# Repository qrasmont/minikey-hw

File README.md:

# Minikey

Mini is a macropad.

## Rev 0.1

### Rev 0.1 Issues

Only related to the BOM.
- Button were not assembled
- R2,R3 are 27K instead of 27 Ohm.

# Characteristics

- 2 rotatry encoders
- 16 keys (Cherry MX, hot swappable)
- USB-C
- RP2040 MCU

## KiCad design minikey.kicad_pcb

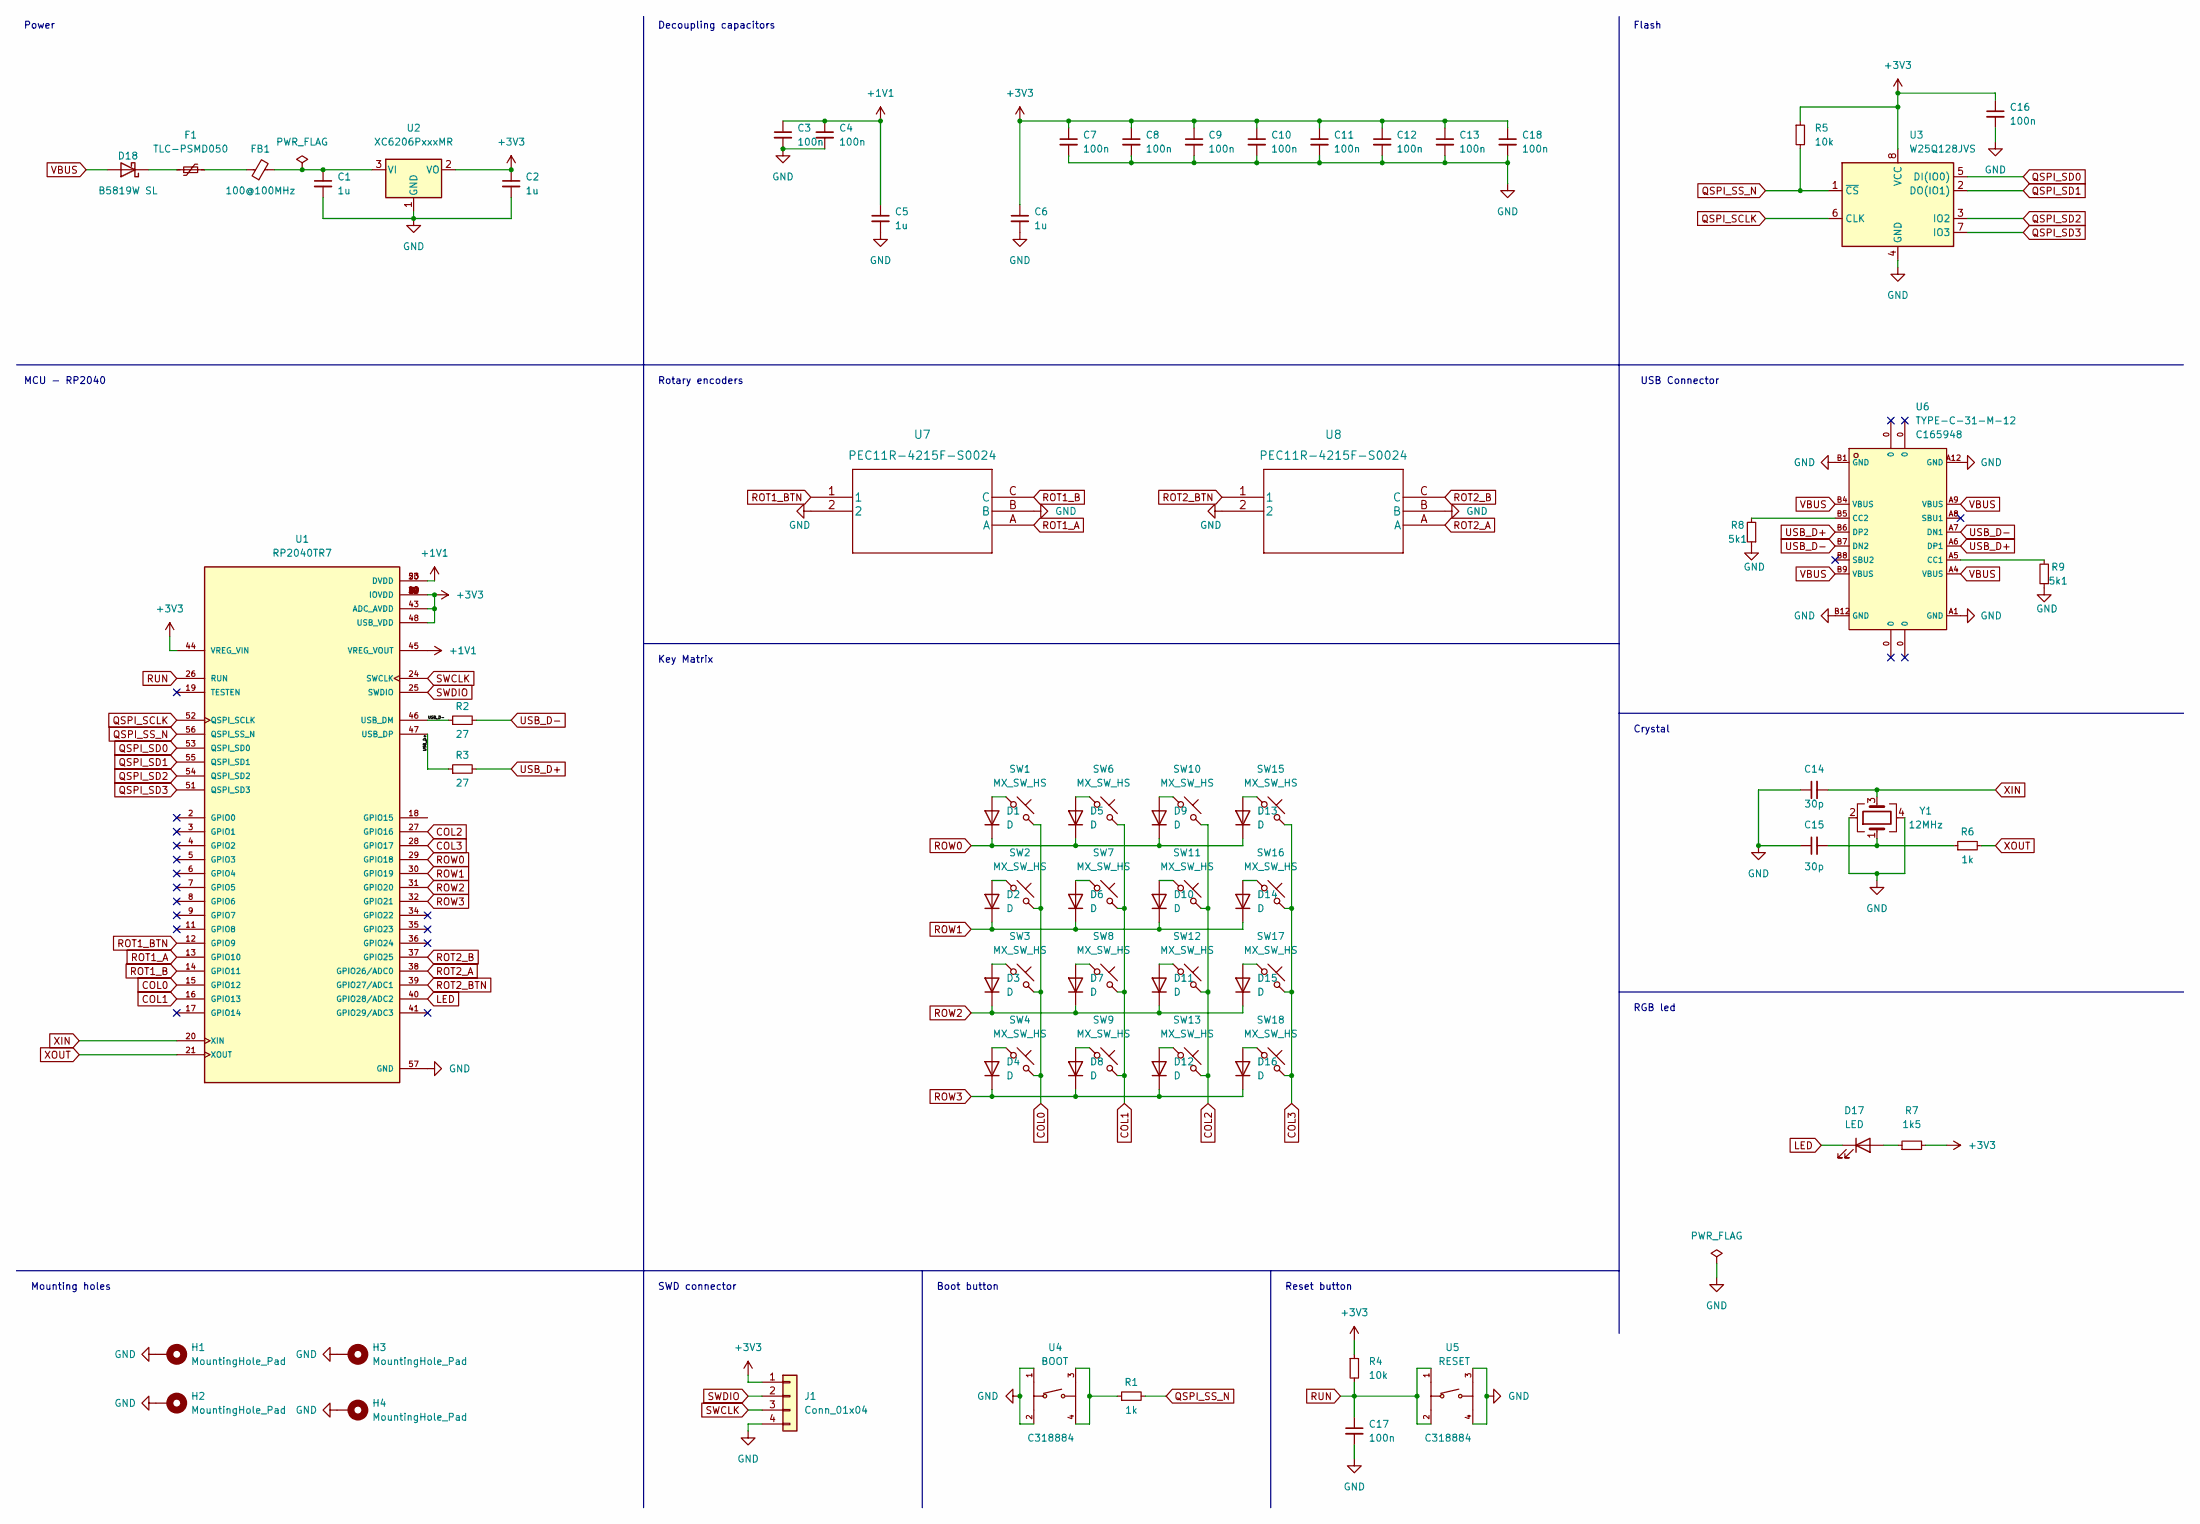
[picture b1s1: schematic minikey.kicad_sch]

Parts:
C1, C2, C5, C6: 1u; C_0402_1005Metric; LCSC Part # C52923
C3, C4, C7, C8, C9, C10, C11, C12, C13, C16, C17, C18: 100n; C_0402_1005Metric; LCSC Part # C307331
C14, C15: 30p; C_0402_1005Metric; LCSC Part # C1570
D1, D2, D3, D4, D5, D6, D7, D8, D9, D10, D11, D12, D13, D14, D15, D16: D; D_SOD-123; LCSC Part # C81598
D17: LED; LED_0805_2012Metric; LCSC Part # C2297
D18: B5819W SL; D_SOD-123; LCSC Part # C8598
F1: TLC-PSMD050; Fuse_0805_2012Metric; LCSC Part # C261942
FB1: 100@100MHz; L_0805_2012Metric; LCSC Part # C1015
H1, H2, H3, H4: MountingHole_Pad; MountingHole_2.2mm_M2_Pad_Via
J1: Conn_01x04; PinHeader_1x04_P2.54mm_Vertical
R1, R6: 1k; R_0402_1005Metric; LCSC Part # C11702
R2, R3: 27; R_0402_1005Metric; LCSC Part # C25190
R4, R5: 10k; R_0402_1005Metric; LCSC Part # C25744
R7: 1k5; R_0402_1005Metric; LCSC Part # C25867
R8, R9: 5k1; R_0402_1005Metric; LCSC Part # C25905
SW1, SW2, SW3, SW4, SW6, SW7, SW8, SW9, SW10, SW11, SW12, SW13, SW15, SW16, SW17, SW18: MX_SW_HS; SW_MX_HS_1u
U1: RP2040TR7; QFN40P700X700X90-57N; PARTREV 1.7.1; LCSC Part # C2040
U2: XC6206PxxxMR; SOT-23; LCSC Part # C5446
U3: W25Q128JVS; SOIC-8_5.23x5.23mm_P1.27mm; LCSC Part # C97521
U4: BOOT; tactile-switch; LCSC C318884
U5: RESET; tactile-switch; LCSC C318884
U6: TYPE-C-31-M-12; simple-usb-c; LCSC C165948
U7, U8: PEC11R-4215F-S0024
Y1: 12MHz; Crystal_SMD_3225-4Pin_3.2x2.5mm; LCSC Part # C9002

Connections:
+1V1: C3.1, C4.1, C5.1, U1.23 (DVDD), U1.45 (VREG_VOUT), U1.50 (DVDD)
+3V3: C2.1, C6.1, C7.1, C8.1, C9.1, C10.1, C11.1, C12.1, C13.1, C16.1, C18.1, J1.1, R4.1, R5.1, R7.2, U1.1 (IOVDD), U1.10 (IOVDD), U1.22 (IOVDD), U1.33 (IOVDD), U1.42 (IOVDD), U1.43 (ADC_AVDD), U1.44 (VREG_VIN), U1.48 (USB_VDD), U1.49 (IOVDD), U2.2 (VO), U3.8 (VCC)
COL0: SW1.2, SW2.2, SW3.2, SW4.2, U1.15 (GPIO12)
COL1: SW6.2, SW7.2, SW8.2, SW9.2, U1.16 (GPIO13)
COL2: SW10.2, SW11.2, SW12.2, SW13.2, U1.27 (GPIO16)
COL3: SW15.2, SW16.2, SW17.2, SW18.2, U1.28 (GPIO17)
GND: C1.2, C2.2, C3.2, C4.2, C5.2, C6.2, C7.2, C8.2, C9.2, C10.2, C11.2, C12.2, C13.2, C14.1, C15.1, C16.2, C17.2, C18.2, H1.1, H2.1, H3.1, H4.1, J1.4, R8.1, R9.1, U1.57 (GND), U2.1 (GND), U3.4 (GND), U4.1 (A), U4.2 (B), U5.3 (C), U5.4 (D), U6.A1 (GND), U6.A12 (GND), U6.B1 (GND), U6.B12 (GND), U7.2, U7.B, U8.2, U8.B, Y1.2, Y1.4
LED: D17.1 (K), U1.40 (GPIO28/ADC2)
unnamed: C1.1, FB1.2, U2.3 (VI)
unnamed: C15.2, R6.1, Y1.1
unnamed: D1.2 (A), SW1.1
unnamed: D2.2 (A), SW2.1
unnamed: D3.2 (A), SW3.1
unnamed: D4.2 (A), SW4.1
unnamed: D5.2 (A), SW6.1
unnamed: D6.2 (A), SW7.1
unnamed: D7.2 (A), SW8.1
unnamed: D8.2 (A), SW9.1
unnamed: D9.2 (A), SW10.1
unnamed: D10.2 (A), SW11.1
unnamed: D11.2 (A), SW12.1
unnamed: D12.2 (A), SW13.1
unnamed: D13.2 (A), SW15.1
unnamed: D14.2 (A), SW16.1
unnamed: D15.2 (A), SW17.1
unnamed: D16.2 (A), SW18.1
unnamed: D17.2 (A), R7.1
unnamed: D18.1 (K), F1.1
unnamed: F1.2, FB1.1
unnamed: R1.1, U4.3 (C), U4.4 (D)
unnamed: R8.2, U6.B5 (CC2)
unnamed: R9.2, U6.A5 (CC1)
QSPI_SCLK: U1.52 (QSPI_SCLK), U3.6 (CLK)
QSPI_SD0: U1.53 (QSPI_SD0), U3.5 (DI(IO0))
QSPI_SD1: U1.55 (QSPI_SD1), U3.2 (DO(IO1))
QSPI_SD2: U1.54 (QSPI_SD2), U3.3 (IO2)
QSPI_SD3: U1.51 (QSPI_SD3), U3.7 (IO3)
QSPI_SS_N: R1.2, R5.2, U1.56 (QSPI_SS_N), U3.1 (~CS)
ROT1_A: U1.13 (GPIO10), U7.A
ROT1_B: U1.14 (GPIO11), U7.C
ROT1_BTN: U1.12 (GPIO9), U7.1
ROT2_A: U1.38 (GPIO26/ADC0), U8.A
ROT2_B: U1.37 (GPIO25), U8.C
ROT2_BTN: U1.39 (GPIO27/ADC1), U8.1
ROW0: D1.1 (K), D5.1 (K), D9.1 (K), D13.1 (K), U1.29 (GPIO18)
ROW1: D2.1 (K), D6.1 (K), D10.1 (K), D14.1 (K), U1.30 (GPIO19)
ROW2: D3.1 (K), D7.1 (K), D11.1 (K), D15.1 (K), U1.31 (GPIO20)
ROW3: D4.1 (K), D8.1 (K), D12.1 (K), D16.1 (K), U1.32 (GPIO21)
RUN: C17.1, R4.2, U1.26 (RUN), U5.1 (A), U5.2 (B)
SWCLK: J1.3, U1.24 (SWCLK)
SWDIO: J1.2, U1.25 (SWDIO)
USB_D+: R3.1, R3.2, U1.47 (USB_DP), U6.A6 (DP1), U6.B6 (DP2)
USB_D-: R2.1, R2.2, U1.46 (USB_DM), U6.A7 (DN1), U6.B7 (DN2)
VBUS: D18.2 (A), U6.A4 (VBUS), U6.A9 (VBUS), U6.B4 (VBUS), U6.B9 (VBUS)
XIN: C14.2, U1.20 (XIN), Y1.3
XOUT: R6.2, U1.21 (XOUT)

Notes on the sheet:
Reset button
Mounting holes
Decoupling capacitors
Power
USB Connector
Rotary encoders
Flash
Crystal
SWD connector
RGB led
Key Matrix
MCU - RP2040
Boot button

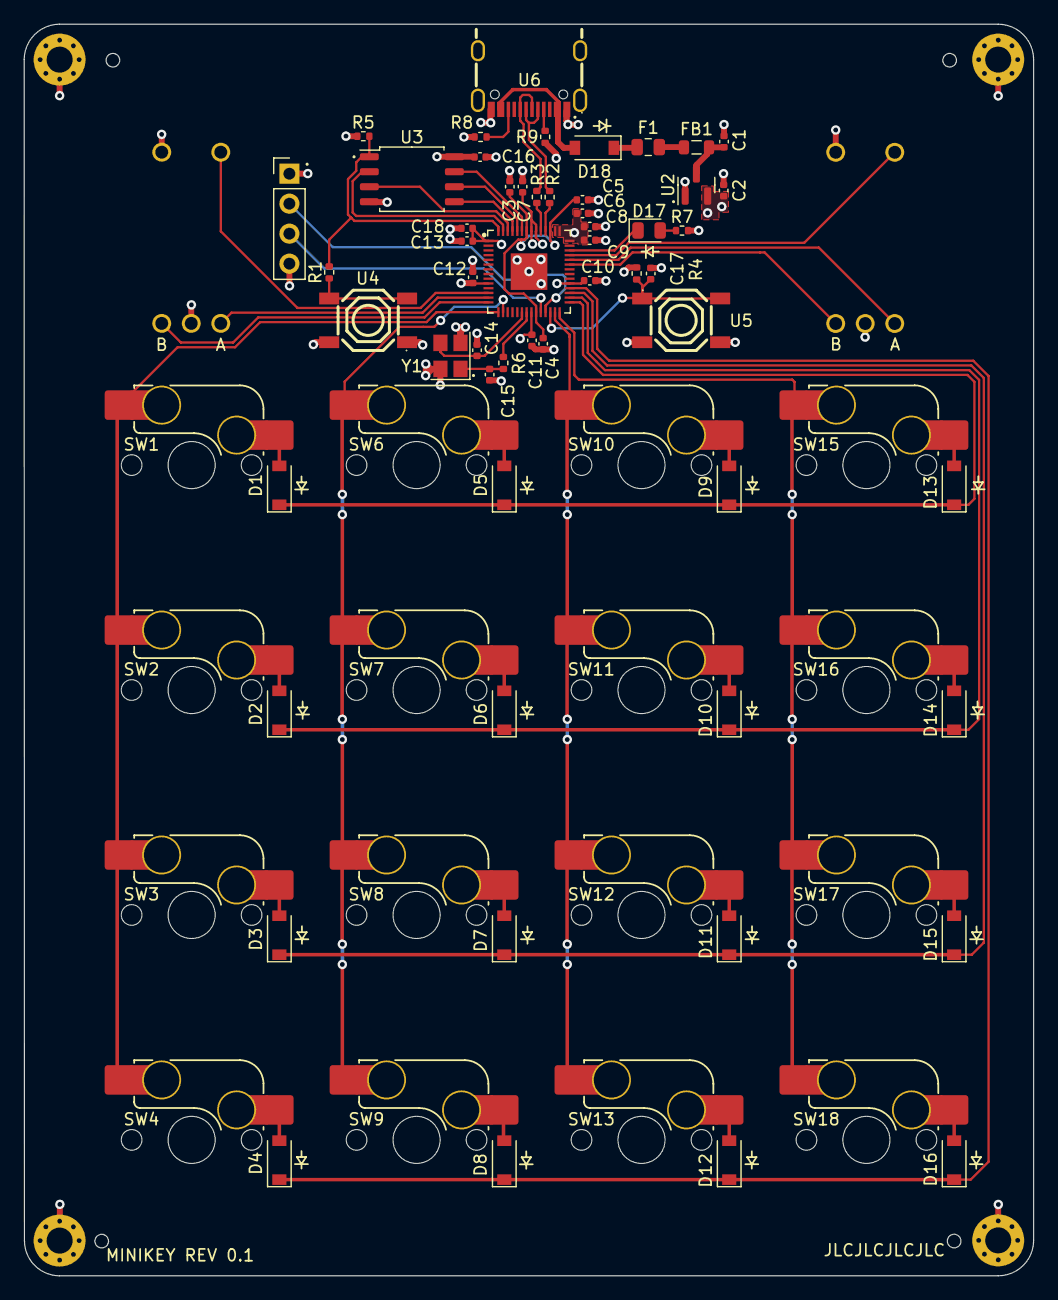
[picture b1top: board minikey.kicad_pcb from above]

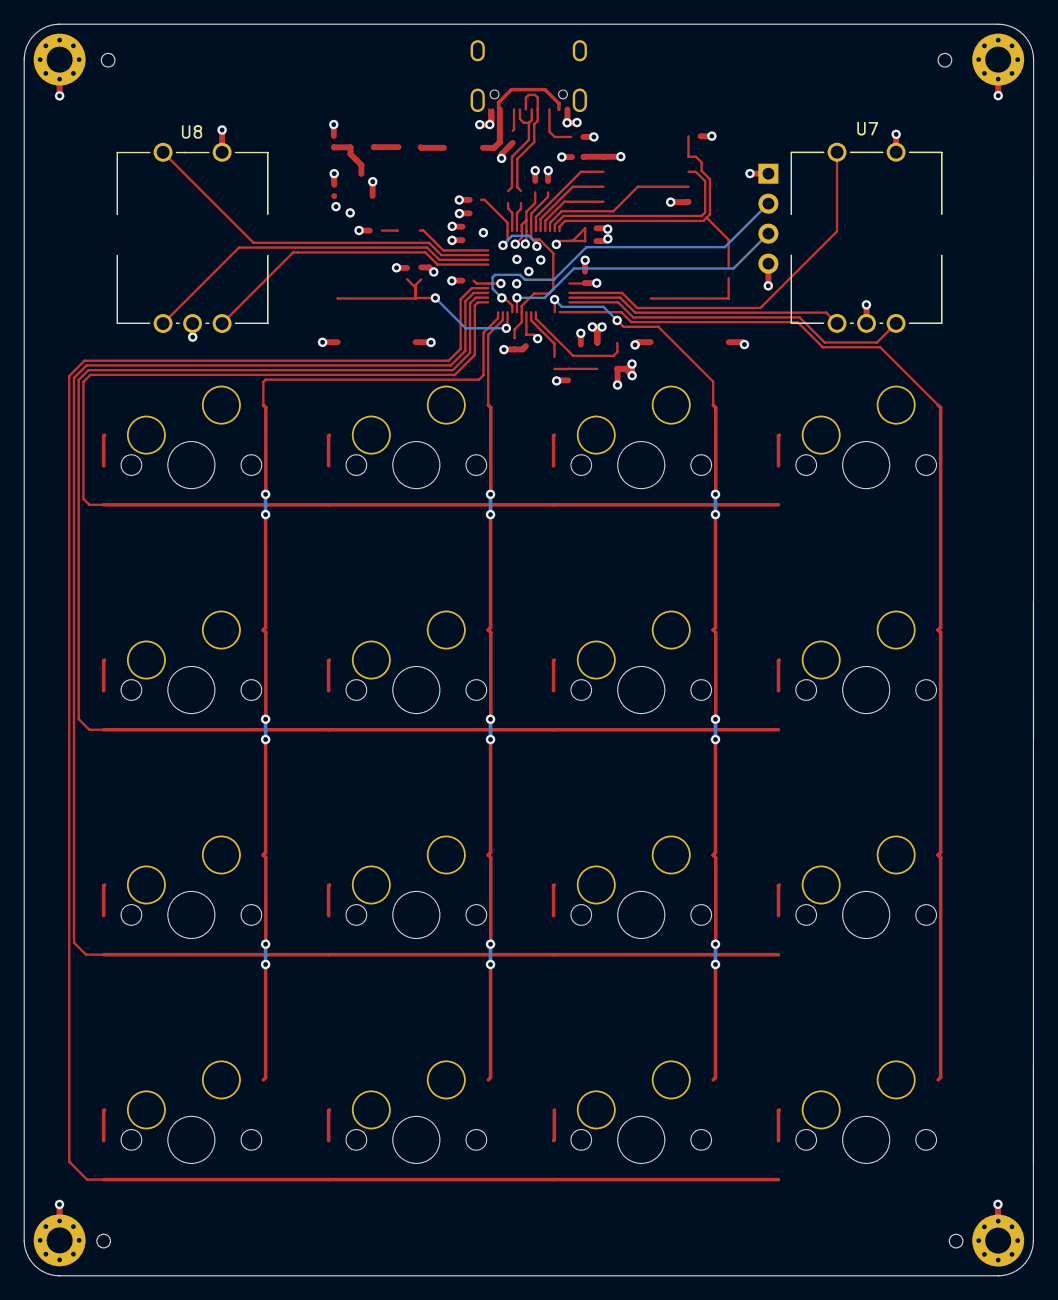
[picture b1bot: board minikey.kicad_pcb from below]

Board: 4 copper layers, 85.5 x 106.0 mm, 77 parts (2 on the bottom side), 56 nets.

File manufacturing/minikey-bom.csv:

Comment,Designator,Footprint,LCSC Part #
"1u Unpolarized capacitor, small symbol","C1,C2,C5,C6",C_0402_1005Metric,C52923
"100n Unpolarized capacitor, small symbol","C3,C4,C7,C8,C9,C10,C11,C12,C13,C16,C17,C18",C_0402_1005Metric,C307331
"30p Unpolarized capacitor, small symbol","C14,C15",C_0402_1005Metric,C1570
D Diode,"D1,D2,D3,D4,D5,D6,D7,D8,D9,D10,D11,D12,D13,D14,D15,D16",D_SOD-123,C81598
LED Light emitting diode,D17,LED_0805_2012Metric,C2297
"B5819W SL 40V 600mV@1A 1A SOD-323 Schottky Barrier Diodes, SOD-323",D18,D_SOD-123,C8598
"TLC-PSMD050 Resettable fuse, polymeric positive temperature coefficient, small symbol",F1,Fuse_0805_2012Metric,C261942
"100@100MHz Ferrite bead, small symbol",FB1,L_0805_2012Metric,C1015
"1k Resistor, small symbol","R1,R6",R_0402_1005Metric,C11702
"27 Resistor, small symbol","R2,R3",R_0402_1005Metric,C25771
"10k Resistor, small symbol","R4,R5",R_0402_1005Metric,C25744
"1k5 Resistor, small symbol",R7,R_0402_1005Metric,C25867
"5k1 Resistor, small symbol","R8,R9",R_0402_1005Metric,C25905
RP2040TR7 ,U1,QFN40P700X700X90-57N,C2040
"XC6206PxxxMR Positive 60-250mA Low Dropout Regulator, Fixed Output, SOT-23",U2,SOT-23,C5446
"W25Q128JVS 128Mb Serial Flash Memory, Standard/Dual/Quad SPI, SOIC-8",U3,SOIC-8_5.23x5.23mm_P1.27mm,C97521
BOOT ,U4,tactile-switch,C318884
RESET ,U5,tactile-switch,C318884
TYPE-C-31-M-12 ,U6,simple-usb-c,C165948
PEC11R-4215F-S0024 ,"U7,U8",PEC11R-4215F-S0024,
"12MHz Four pin crystal, GND on pins 2 and 4",Y1,Crystal_SMD_3225-4Pin_3.2x2.5mm,C9002

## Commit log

2023-04-01 Add files for rev 0.1
2023-04-01 Add README
2023-04-17 Add rev 0.1 pictures
2023-04-17 Add note on rev 0.1 issues

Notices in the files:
parts and their libraries:
Copyright 2021 Accelerated Designs. All rights reserved.
